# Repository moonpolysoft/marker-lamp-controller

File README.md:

# F-150 Lightning Auxiliary Marker-Lamp Controller

An open-hardware controller that makes aftermarket amber grille marker lamps
follow the factory parking lamps on a 2023 Ford F-150 Lightning—without using
the CAN bus or trailer-lighting outputs.

## Status

- Revision A was assembled, bench tested, and verified in the vehicle.
- The selected driver-side rear parking-lamp signal provides the desired lamp
  behavior. No front-lamp or CAN connection is required.
- Revision B corrects the three assembly issues found on Revision A. A
  Revision B board has been assembled, bench tested, installed, and verified
  working in the vehicle.
- The current enclosure prototype has been printed and its mechanical fit is
  confirmed, including the revised connector opening, boss clearances, and
  recessed lid screws.

This remains a hobbyist engineering prototype, not a Ford-approved accessory
or a safety-certified automotive product. Read [Safety](#safety) before
building or installing it.

## Finished build

The completed controller follows the selected factory parking-lamp signal and
switches the three aftermarket amber grille lamps as intended.

[Play or download the installation demonstration (MP4, H.264/AAC)](docs/media/lighting-working.mp4)

## What it does

The controller senses the factory rear parking-lamp output through an
optocoupler and drives the aftermarket LEDs from a separate fused 12 V supply
using a protected high-side switch. The factory lamp circuit supplies only the
sense current; it does not power the added lamps.

```text
Factory rear parking-lamp output ── isolated sense/filter ──┐
                                                            │
Fused 12 V supply ── protected high-side switch ── marker lamps
Vehicle ground ─────────────────────────────────── marker return
```

The tested aftermarket lamp assembly draws approximately 0.25 A with the
vehicle low-voltage system energized. The observed sense signal reads roughly
6 V with the truck off and 8 V with it on when measured by a multimeter,
consistent with a pulse-width-modulated automotive lamp output.

## Repository contents

| Path | Contents |
|---|---|
| [`hardware/kicad/`](hardware/kicad/) | KiCad boards, deterministic PCB generator, BOM, DRC reports, Gerbers, drill files, and OSH Park upload archives |
| [`hardware/controller-design.md`](hardware/controller-design.md) | Circuit architecture, component rationale, and validation notes |
| [`enclosure/`](enclosure/) | Parametric OpenSCAD enclosure source and printable STL exports |
| [`docs/rear-parking-wire-test.md`](docs/rear-parking-wire-test.md) | Procedure used to identify and verify the vehicle signal |
| [`docs/media/`](docs/media/) | Finished controller photo and in-vehicle demonstration video |

Revision B is the current PCB. Revision A files remain available as design
history but include known assembly defects; do not order Revision A.

## Building the board

The easiest fabrication input is:

[`hardware/kicad/fabrication-rev-b/marker-lamp-controller-rev-b-oshpark.zip`](hardware/kicad/fabrication-rev-b/marker-lamp-controller-rev-b-oshpark.zip)

The board is a two-layer, 80 × 45 mm design made for OSH Park's standard
two-layer service. Review the current [`BOM.csv`](hardware/kicad/BOM.csv),
because distributor stock and manufacturer lifecycle status change over time.
Connector pinout, board specifications, regeneration instructions, and known
Revision A defects are documented in the
[`hardware/kicad/README.md`](hardware/kicad/README.md).

To regenerate the PCB source with KiCad 10's Python environment:

```sh
python3 hardware/kicad/generate_pcb.py
```

The generator and
[`circuit-netlist.md`](hardware/kicad/circuit-netlist.md) are the authoritative
circuit sources. This project currently does not contain a conventional KiCad
schematic.

## Printing the enclosure

Open [`controller_enclosure.scad`](enclosure/controller_enclosure.scad) in
OpenSCAD and select `base` or `lid`, or print the supplied STL files. See the
[`enclosure/README.md`](enclosure/README.md) for hardware dimensions, material
recommendations, and print settings. The lid should be printed with a 5 mm
brim.

## Installation summary

J1 uses a Same Sky `TBP01R1-508-04BE` board header with a
`TBP01P1-508-04BE` wire-side plug:

| Pin | Signal | Connection |
|---:|---|---|
| 1 | `SENSE` | Verified parking-lamp signal tap |
| 2 | `BATT+` | Separately fused 12 V supply |
| 3 | `LAMP+` | Switched positive output to marker LEDs |
| 4 | `GND` | Chassis ground and lamp return |

Place the branch fuse near the power source. The design documentation calls
for a 2 A fuse and 18 AWG automotive primary wire for the tested 0.25 A load.
Confirm wiring, fuse size, polarity, and connector numbering against your own
vehicle and hardware; model-year and trim wiring can differ.

## Safety

Automotive electrical systems can produce load-dump, inductive, reverse-
polarity, and electrostatic transients. A wiring fault can damage vehicle
modules or start a fire. Disconnect the low-voltage battery as directed by the
vehicle service procedure before permanent wiring, protect added conductors
with an appropriately placed fuse, use automotive-rated wire and abrasion
protection, and secure the assembly away from heat, water, sharp edges, and
moving parts.

Do not treat a zero-error DRC result as validation of electrical safety. Test
every assembled board with a current-limited bench supply before vehicle use.
You build and install this project at your own risk.

Ford and F-150 Lightning are trademarks of their respective owner. This
project is independent and is not affiliated with or endorsed by Ford Motor
Company.

## Contributing

Bug reports, measurements, documentation corrections, and design improvements
are welcome. See [`CONTRIBUTING.md`](CONTRIBUTING.md) before submitting a
change. In particular, identify the PCB revision and vehicle model year/trim
when reporting electrical behavior.

## License

This project is open hardware licensed under the
[CERN Open Hardware Licence Version 2—Strongly Reciprocal](LICENSE), SPDX
identifier `CERN-OHL-S-2.0`.

You may use, study, modify, manufacture, and distribute the design subject to
the licence terms. The strongly reciprocal variant was selected so that
distributed modified designs and products remain accompanied by corresponding
design source. The licence includes warranty and liability disclaimers; it is
not a certification of fitness for automotive use.

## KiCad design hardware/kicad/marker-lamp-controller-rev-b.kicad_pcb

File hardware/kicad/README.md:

# Fabrication Design

This directory contains Revision A and Revision B of the two-layer
marker-lamp controller. Revision B is the current fabrication design.

## Files

- `marker-lamp-controller.kicad_pcb` — generated KiCad 10 PCB.
- `marker-lamp-controller-rev-b.kicad_pcb` — corrected Revision B PCB.
- `generate_pcb.py` — deterministic PCB generator using KiCad's `pcbnew`
  Python module.
- `circuit-netlist.md` — readable authoritative circuit connectivity.
- `revision-b-notes.md` — corrections found while assembling Revision A that
  must be incorporated before the next board order.
- `BOM.csv` — orderable manufacturer and DigiKey part numbers.
- `drc-report.txt` — KiCad board DRC result.
- `fabrication/` — OSH Park Gerbers and separate plated/non-plated drills.
- `fabrication-rev-b/` — Revision B OSH Park Gerbers, drills, and upload ZIP.
- `board-render.png` — top-side board preview (custom hand-solder footprints
  do not carry 3D body models).
- `board-render-rev-b.png` — Revision B top-side board preview.

Revision B includes top-side reference designators, diode cathode markings,
C3 polarity, U1/U2 pin-1 cues, Q1 lead labels, the complete J1 pinout, and the
project source URL to support hand assembly and design-source identification.

The PCB generator and `circuit-netlist.md` are authoritative for Revision B.

## Connector

Board header:

- Same Sky `TBP01R1-508-04BE`

Mating pluggable terminal connector:

- Same Sky `TBP01P1-508-04BE`

Pinout:

1. `SENSE` — driver-side rear parking output, C4483 cavity 10,
   violet/green.
2. `BATT+` — separately fused 12 V feed; use a 2 A fuse.
3. `LAMP+` — switched positive output to the 0.25 A grille LEDs.
4. `GND` — chassis ground and grille LED return.

## Board construction

- 80 × 45 mm
- Two copper layers
- 1 oz copper
- Minimum designed trace/space: 0.20 mm / 0.20 mm
- Signal traces: 0.35–0.60 mm
- Power/load traces: 1.2 mm
- Vias: 0.8 mm finished pad, 0.4 mm drill
- Four 3.2 mm non-plated mounting holes
- Mounting-hole centers: 72 × 37 mm
- Components on the top side

These values exceed the OSH Park two-layer minima of 0.1524 mm
trace/spacing, 0.127 mm annular ring, and 0.254 mm minimum drill.

## DigiKey availability review

The BOM was checked against DigiKey stock on 2026-07-24. Stock changes
continuously, so verify it again before ordering.

- BSP762TXUMA1: stocked, cut tape available.
- VO617A-4X017T: stocked, cut tape available.
- TBP01R1-508-04BE header: stocked.
- TBP01P1-508-04BE mating plug: stocked.
- STPS2H100A and SMBJ22A: stocked, cut tape available.
- SBC807-40LT1G: stocked, automotive-qualified.
- 1N4148WS: stocked alternate selected.
- BZT52-C5V1-QX: stocked, automotive-qualified.
- CGA6P1X7R1E106K250AC: stocked, automotive-qualified.
- C0805C104K5RAC7210: stocked, active replacement for an obsolete Murata
  bypass capacitor considered during selection.
- EEE-FK1H470P and all three Yageo resistor values: stocked.

## Regenerate

```sh
python3 generate_pcb.py
```

Run from this directory or from the project root using the full relative path.

Generate the top-side repository preview from the project root with:

```sh
kicad-cli pcb render --side top --quality basic --background opaque \
  --width 1600 --height 900 --zoom 1.15 \
  -o hardware/kicad/board-render-rev-b.png \
  hardware/kicad/marker-lamp-controller-rev-b.kicad_pcb
```

The custom hand-solder footprints do not include 3D component-body models, so
the render intentionally shows the bare board, pads, and assembly silkscreen.

## Status

An assembled Revision B board has been bench tested, installed, and verified
working in the vehicle with the intended 0.25 A marker-lamp load. It remains an
engineering prototype; independent builders should bench test every assembly
and characterize turn-on/off behavior, reverse polarity, output short
protection, thermal behavior, and vehicle sleep current before permanent
installation.

KiCad 10 DRC reports zero violations, zero unconnected pads, and zero footprint
errors for Revision B. This verifies the artwork rules and connectivity, not
vehicle behavior.

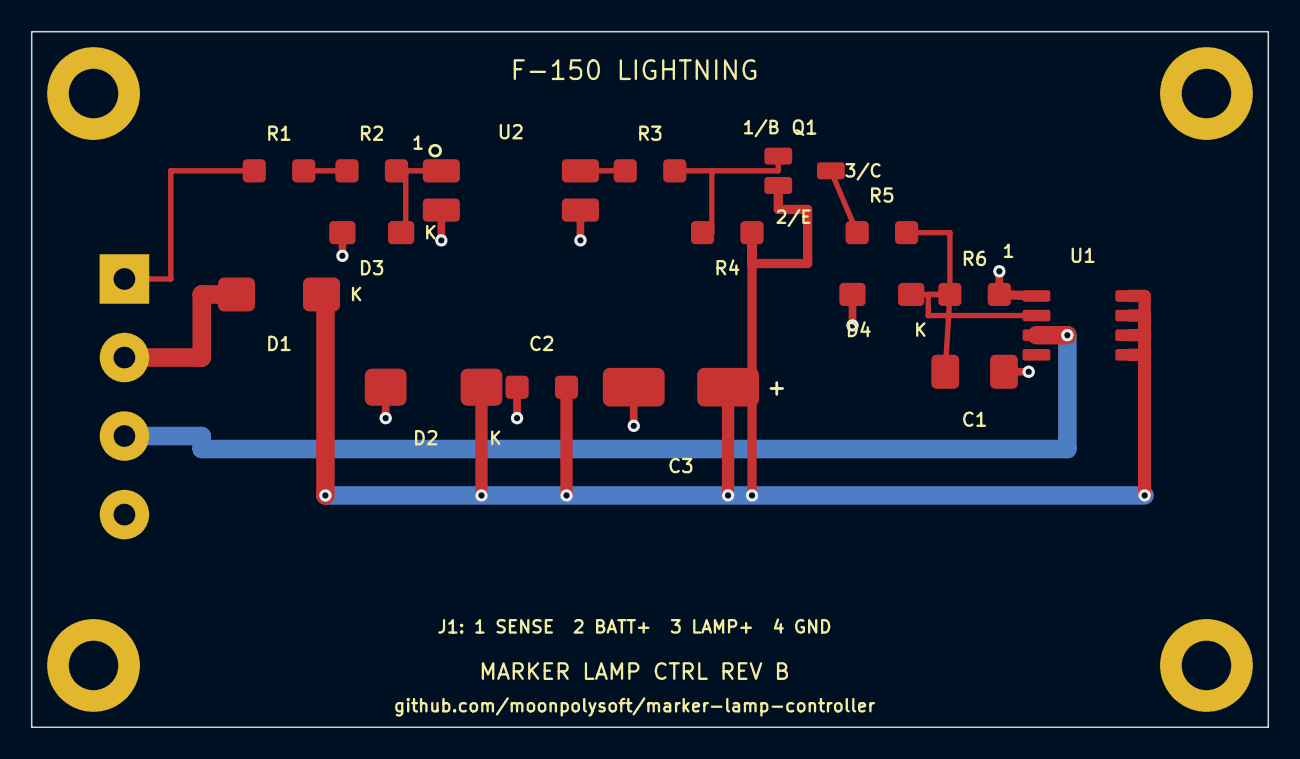
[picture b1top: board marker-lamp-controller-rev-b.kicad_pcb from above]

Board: 2 copper layers, 80.0 x 45.0 mm, 21 parts (0 on the bottom side), 11 nets.

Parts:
C1: 10u 25V
C2: 100n 50V
C3: 47u 50V
D1: STPS2H100A
D2: SMBJ22A
D3: 1N4148WS
D4: BZT52C5V1
H1, H2, H3, H4: M3
J1: TBP01R1-508-04BE
Q1: BC807-40
R1, R2: 1k
R3, R5: 10k
R4, R6: 100k
U1: BSP762TXUMA1
U2: VO617A-4X017T

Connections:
CTRL: C1.1, D4.1, R5.2, R6.1, U1.2
GND: C1.2, C2.1, C3.2, D2.2, D3.2, D4.2, J1.4, R6.2, U1.1, U2.2, U2.3
LAMP_OUT: J1.3, U1.3
OPTO_A: D3.1, R2.2, U2.1
OPTO_C: R3.1, U2.4
QBASE: Q1.1, R3.2, R4.1
QCOL: Q1.3, R5.1
SENSE: J1.1, R1.1
SENSE_R1: R1.2, R2.1
VPRE: D1.2, J1.2
VPWR: C2.2, C3.1, D1.1, D2.1, Q1.2, R4.2, U1.5, U1.6, U1.7, U1.8
